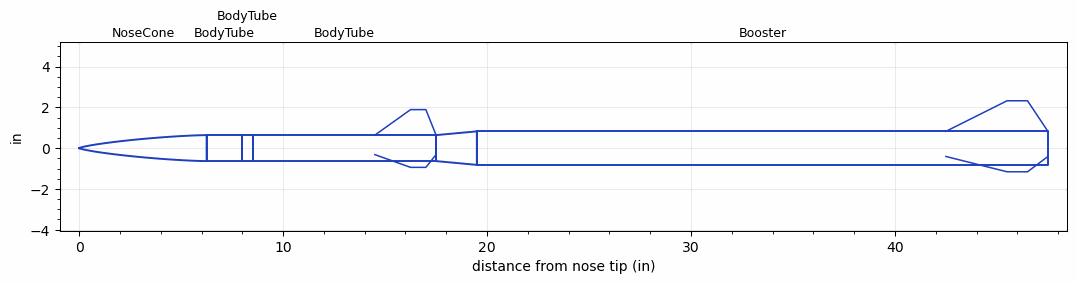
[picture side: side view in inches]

<RASAeroDocument>
 <FileVersion>2</FileVersion>
 <RocketDesign>
  <NoseCone>
   <Length>6.25</Length>
   <Diameter>1.274</Diameter>
   <Shape>Von Karman Ogive</Shape>
   <Location>0</Location>
  </NoseCone>
  <BodyTube>
   <Length>1.75</Length>
   <Diameter>1.274</Diameter>
   <Location>6.25</Location>
  </BodyTube>
  <BodyTube>
   <Length>0.5</Length>
   <Diameter>1.274</Diameter>
   <Location>8</Location>
  </BodyTube>
  <BodyTube>
   <Length>9</Length>
   <Diameter>1.274</Diameter>
   <RailGuideDiameter>0.4375</RailGuideDiameter>
   <RailGuideHeight>0.2975</RailGuideHeight>
   <Location>8.5</Location>
   <Fin>
    <Count>3</Count>
    <Chord>3</Chord>
    <Span>1.25</Span>
    <SweepDistance>1.75</SweepDistance>
    <TipChord>0.75</TipChord>
    <Thickness>0.1</Thickness>
    <Location>3</Location>
    <AirfoilSection>Square</AirfoilSection>
   </Fin>
  </BodyTube>
  <Booster>
   <Length>27.9999</Length>
   <Diameter>1.644</Diameter>
   <InsideDiameter>1.274</InsideDiameter>
   <Location>17.5</Location>
   <ShoulderLength>2</ShoulderLength>
   <Fin>
    <Count>3</Count>
    <Chord>5</Chord>
    <Span>1.5</Span>
    <SweepDistance>3</SweepDistance>
    <TipChord>1</TipChord>
    <Thickness>0.1</Thickness>
    <Location>5</Location>
    <AirfoilSection>Square</AirfoilSection>
   </Fin>
  </Booster>
  <Surface>Camouflage Paint</Surface>
  <ModifiedBarrowman>True</ModifiedBarrowman>
  <Turbulence>False</Turbulence>
  <UseBooster1>True</UseBooster1>
  <UseBooster2>False</UseBooster2>
  <Comments>It's kinda cursed</Comments>
 </RocketDesign>
 <LaunchSite>
  <Altitude>800</Altitude>
  <Pressure>29.0769</Pressure>
  <RodAngle>2</RodAngle>
  <RodLength>71.9999</RodLength>
  <Temperature>56.1471</Temperature>
  <WindSpeed>8</WindSpeed>
 </LaunchSite>
 <Recovery>
  <Altitude1>600</Altitude1>
  <Altitude2>656.168</Altitude2>
  <DeviceType1>Parachute</DeviceType1>
  <DeviceType2>Parachute</DeviceType2>
  <Event1>True</Event1>
  <Event2>True</Event2>
  <Size1>24</Size1>
  <Size2>29.9999</Size2>
  <EventType1>Altitude</EventType1>
  <EventType2>Apogee</EventType2>
  <CD1>0.5</CD1>
  <CD2>0.5</CD2>
 </Recovery>
 <SimulationList>
  <Simulation>
   <SustainerEngine>Dart  (NoThrust)</SustainerEngine>
   <SustainerLaunchWt>1.21</SustainerLaunchWt>
   <SustainerCG>10.7</SustainerCG>
   <SustainerIgnitionDelay>0</SustainerIgnitionDelay>
   <Booster1Engine>I540WT  (CTI)</Booster1Engine>
   <Booster1LaunchWt>3.5</Booster1LaunchWt>
   <Booster1SeparationDelay>0</Booster1SeparationDelay>
   <Booster1IgnitionDelay>0</Booster1IgnitionDelay>
   <Booster1CG>26.45</Booster1CG>
   <IncludeBooster1>True</IncludeBooster1>
   <Booster2Delay>0</Booster2Delay>
   <IncludeBooster2>False</IncludeBooster2>
   <TimetoApogee>14.0602</TimetoApogee>
   <MaxAltitude>4846.167</MaxAltitude>
   <MaxVelocity>1167.974</MaxVelocity>
  </Simulation>
  <Simulation>
   <SustainerEngine>Dart  (NoThrust)</SustainerEngine>
   <SustainerLaunchWt>1.21</SustainerLaunchWt>
   <SustainerCG>10.7</SustainerCG>
   <SustainerIgnitionDelay>0</SustainerIgnitionDelay>
   <Booster1Engine>J500G  (AT)</Booster1Engine>
   <Booster1LaunchWt>3.83</Booster1LaunchWt>
   <Booster1SeparationDelay>0</Booster1SeparationDelay>
   <Booster1IgnitionDelay>0</Booster1IgnitionDelay>
   <Booster1CG>27.35</Booster1CG>
   <IncludeBooster1>True</IncludeBooster1>
   <Booster2Delay>0</Booster2Delay>
   <IncludeBooster2>False</IncludeBooster2>
   <TimetoApogee>14.3402</TimetoApogee>
   <MaxAltitude>5109.157</MaxAltitude>
   <MaxVelocity>1143.277</MaxVelocity>
  </Simulation>
  <Simulation>
   <SustainerLaunchWt>1.2089</SustainerLaunchWt>
   <SustainerCG>10.7044</SustainerCG>
   <SustainerIgnitionDelay>0</SustainerIgnitionDelay>
   <Booster1LaunchWt>3.2964</Booster1LaunchWt>
   <Booster1SeparationDelay>0</Booster1SeparationDelay>
   <Booster1IgnitionDelay>0</Booster1IgnitionDelay>
   <Booster1CG>26.5148</Booster1CG>
   <IncludeBooster1>True</IncludeBooster1>
   <Booster2Delay>0</Booster2Delay>
   <IncludeBooster2>False</IncludeBooster2>
  </Simulation>
  <Simulation>
   <SustainerLaunchWt>1.2089</SustainerLaunchWt>
   <SustainerCG>10.7044</SustainerCG>
   <SustainerIgnitionDelay>0</SustainerIgnitionDelay>
   <Booster1LaunchWt>3.5326</Booster1LaunchWt>
   <Booster1SeparationDelay>0</Booster1SeparationDelay>
   <Booster1IgnitionDelay>0</Booster1IgnitionDelay>
   <Booster1CG>27.0291</Booster1CG>
   <IncludeBooster1>True</IncludeBooster1>
   <Booster2Delay>0</Booster2Delay>
   <IncludeBooster2>False</IncludeBooster2>
  </Simulation>
  <Simulation>
   <SustainerLaunchWt>1.2089</SustainerLaunchWt>
   <SustainerCG>10.7044</SustainerCG>
   <SustainerIgnitionDelay>0</SustainerIgnitionDelay>
   <Booster1LaunchWt>3.5129</Booster1LaunchWt>
   <Booster1SeparationDelay>0</Booster1SeparationDelay>
   <Booster1IgnitionDelay>0</Booster1IgnitionDelay>
   <Booster1CG>26.9551</Booster1CG>
   <IncludeBooster1>True</IncludeBooster1>
   <Booster2Delay>0</Booster2Delay>
   <IncludeBooster2>False</IncludeBooster2>
  </Simulation>
 </SimulationList>
</RASAeroDocument>
